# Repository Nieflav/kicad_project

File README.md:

# Arduino Gas Sensor shield

This PCB was created using KiCad. The schematic has been created from an Arduino Uno shield template. As a consequence, this board will be easily pluggable on top of an Arduino Uno. This board includes a TO-5 package socket for the gas sensor [U4] (supplied by the +3V3 output of the Arduino [pin 4]).

## Sensor operation

A conditioner circuit, based on an operational amplifier [U1] (supplied on the +5V output of the Arduino[pin 5]), is included to amplify and filter the signal before it can be received by the Arduino on a analog input [A2].

Another analog input [A1] is used for temperature monitoring of the gas. The [pin 3] (output) is connected to the  heat resistor of the sensor to control the operating temperature. 

Two jumpers [J2 & J3] are used to choose the gas sensor (between the two available on the package [RSense1 & RSense2]) for the input of the conditioner. They have to be on the same position.

A comparator [U3] (based on an other operational amplifier ) used to detect a anormal value of gas defined by a voltage reference given by the Arduino [pin 6] (PWM). This allows the Arduino to be in sleep mode and to be woken up with an interrupt from the output of the aplifier [pin 2].

## LoRA feature

A RN2483 module is included on the shield, ready to be soldered on it. It transmits a LoRA message on TheThingsNetwork platform in case of anormal gas value. It communicates using UART through its [pins 6 & 7] to the [pins 10 & 11] of the Arduino.
The RN2483 module is powered through [pin 12] with the +5V output of the Arduino.

An antenna has to be connected to the [pin 23] to transmit the LoRA messages. It can be installed through a SMA connector [J1].

A gound plane has been added on both faces (top and bottom). Every components can be soldered on the top face (included the gas sensor package and the two operational amplifier which are THT).

All the SMD components are 1206_3216 Metric.

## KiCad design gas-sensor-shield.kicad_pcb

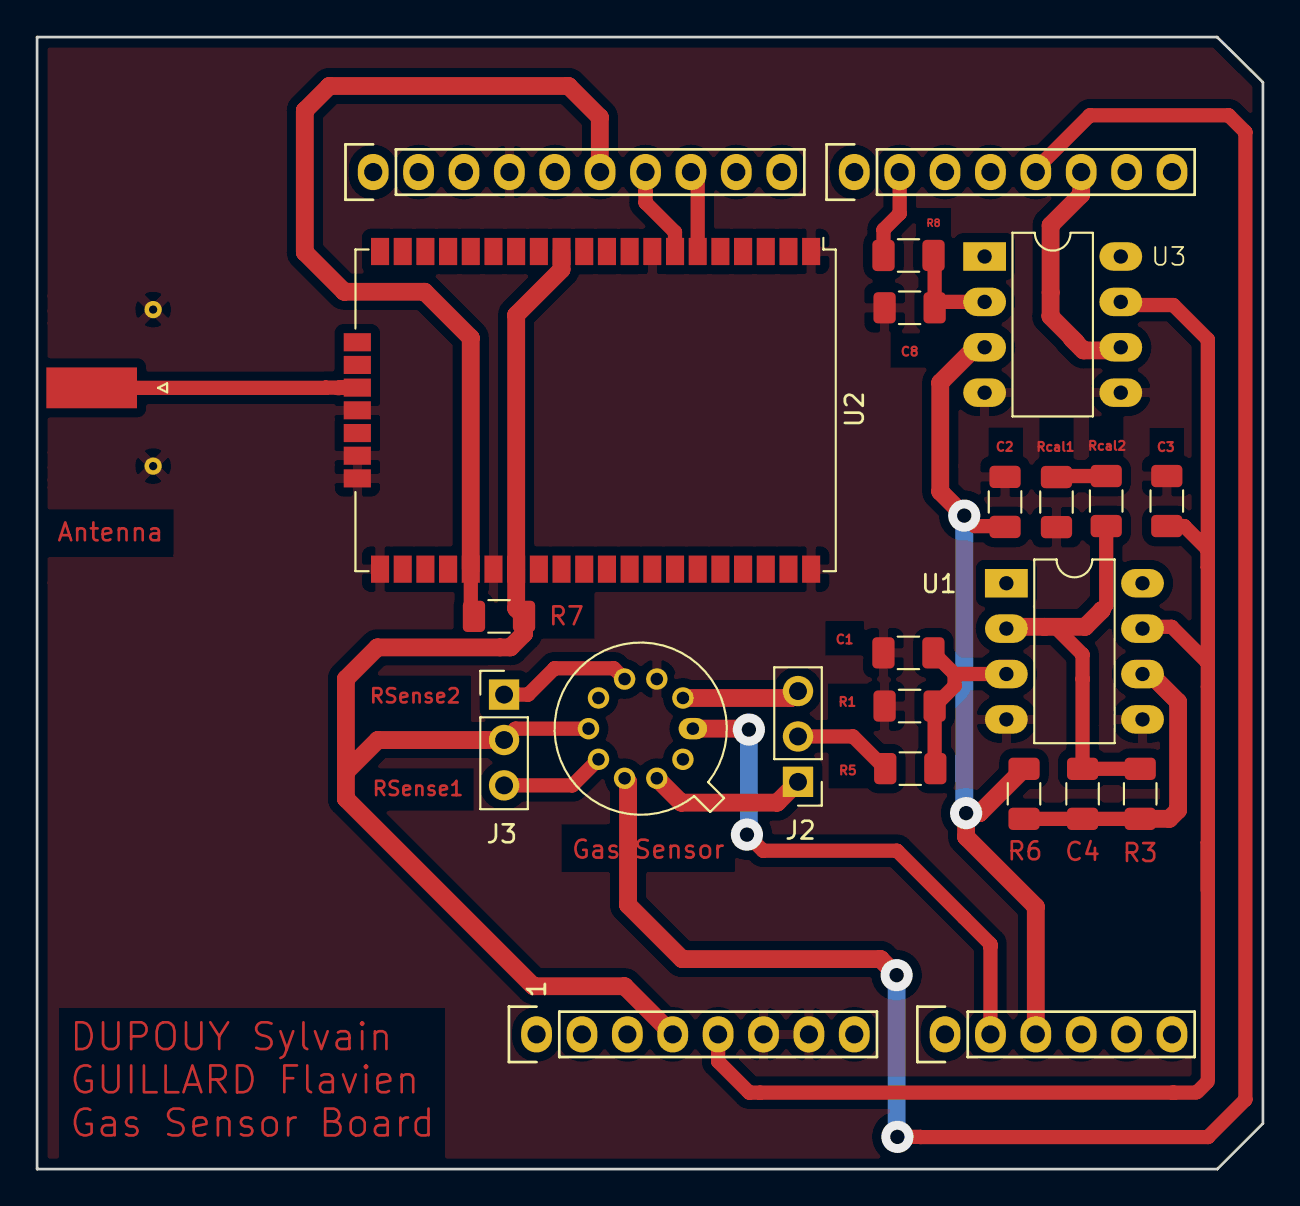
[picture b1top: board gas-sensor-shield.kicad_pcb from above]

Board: 2 copper layers, 68.6 x 63.4 mm, 24 parts (0 on the bottom side), 24 nets.

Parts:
Antenna: Conn_Coaxial; SMA_Molex_73251-1153_EdgeMount_Horizontal
C1, C2, C3: 100n; C_1206_3216Metric
C4: 1u; C_1206_3216Metric
C8: 0,1u; C_1206_3216Metric
Gas Sensor: GazSensor; TO-5-10
J2, J3: Conn_01x03; PinHeader_1x03_P2.54mm_Vertical
P1: Power; Socket_Strip_Arduino_1x08
P2: Analog; Socket_Strip_Arduino_1x06
P3: Digital; Socket_Strip_Arduino_1x10
P4: Digital; Socket_Strip_Arduino_1x08
R1, R3, R5, R8: 100K; R_1206_3216Metric
R6: 1K; R_1206_3216Metric
R7: 10K; R_1206_3216Metric
Rcal1, Rcal2: R; R_1206_3216Metric
U1, U3: LTC1050; DIP-8_W7.62mm_LongPads
U2: RN2483

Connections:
!RST: P3.6, R7.2, U2.32
+3V3: Gas Sensor.6, J3.2, P1.4, R7.1, U2.12, U2.34
+5V: C3.1, U1.7, U3.7
/A4(SDA): P2.5, P3.2
/A5(SCL): P2.6, P3.1
ANT: Antenna.1, U2.23
ANxArduino: C2.1, P2.3, R6.1, U3.3
CapTemp: Gas Sensor.1, P2.2
GND: Antenna.2, C1.2, C2.2, C3.2, C8.2, Gas Sensor.3, P1.6, P1.7, P3.4, R1.2, Rcal1.1, U1.4, U1.5, U2.1, U2.8, U2.24, U2.26, U2.27, U2.28, U2.33, U2.47, U3.4, U3.5
INT: P4.6, U3.6
unnamed: C1.1, R1.1, R5.2, U1.3
unnamed: C4.1, R3.1, Rcal2.2, U1.2
unnamed: C4.2, R3.2, R6.2, U1.6
unnamed: C8.1, R8.2, U3.2
unnamed: Gas Sensor.9, J2.1
unnamed: Gas Sensor.2, J2.3
unnamed: Gas Sensor.4, J3.1
unnamed: Gas Sensor.7, J3.3
unnamed: Rcal1.2, Rcal2.1
RChauff: Gas Sensor.8, P4.5
RX: P3.7, U2.7
Rsensor: J2.2, R5.1
TX: P3.8, U2.6
Vref: P4.2, R8.1

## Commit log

2019-11-12 first schematic
2019-11-12 creation of first pcb kicad
2019-11-21 pcb almost designed
2019-11-21 pcb redesigned and resized, gnd plane missing
2019-11-25 last version of PCB
2019-12-02 pcb with 8 pins
2019-12-19 final version
2019-12-19 final version- useless files deleted
2019-12-22 updated gitignore
2019-12-22 move project root and rename project
2020-01-21 add entire lib
2020-01-21 pictures
2020-01-22 RN2483 lib
2020-01-22 updated 3d view
